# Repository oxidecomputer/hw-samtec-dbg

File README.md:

# hw-samtec-dbg

Allows for conversion between SFM-105-02-X-DH-XX, TFC-105-02-F-D-A-K, and a 2x5 0.1" header.

# Status
CAD represents a functional design without modifications

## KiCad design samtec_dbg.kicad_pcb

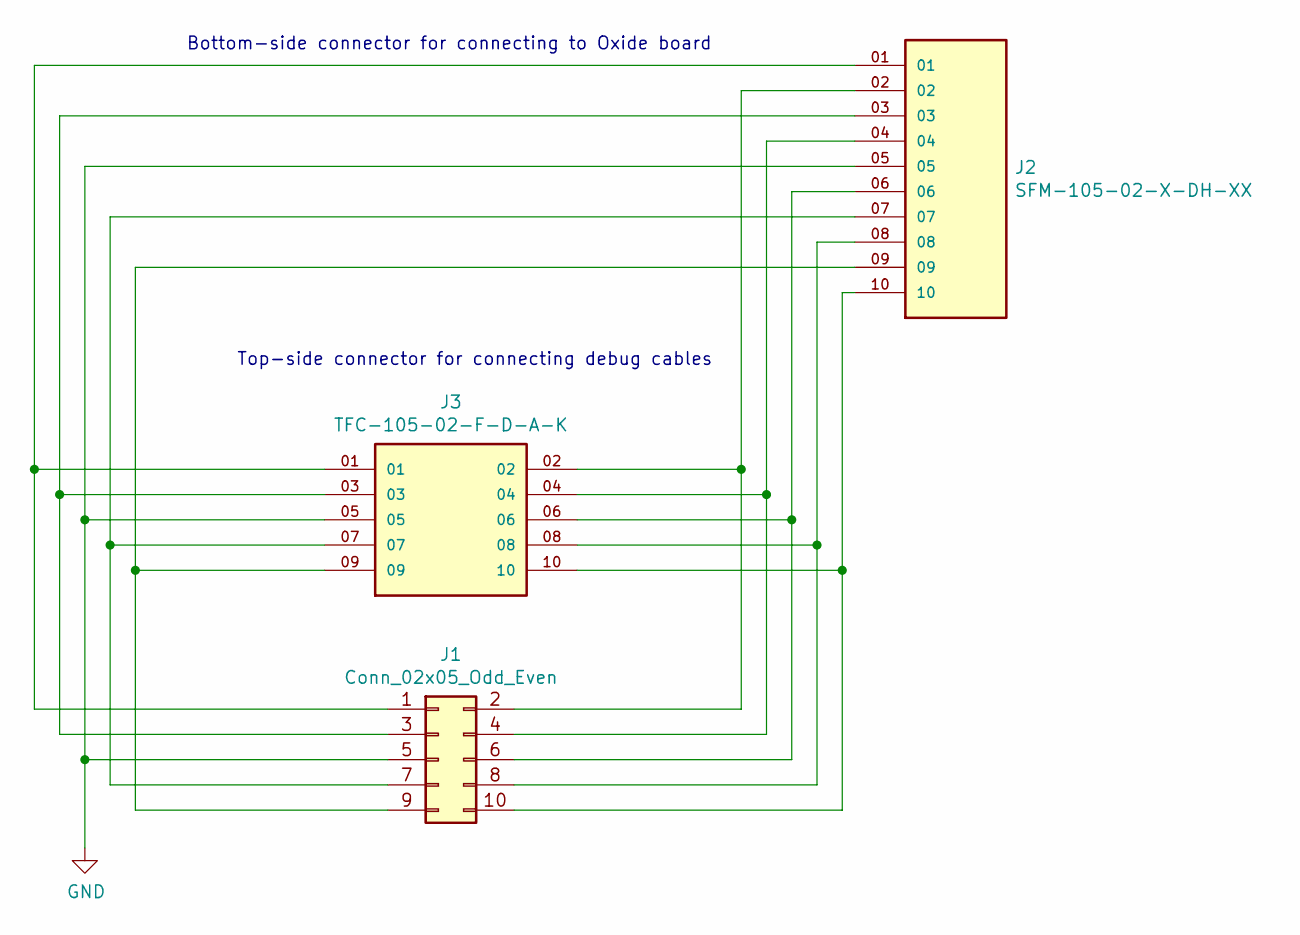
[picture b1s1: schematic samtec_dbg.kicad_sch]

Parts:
J1: Conn_02x05_Odd_Even; PinHeader_2x05_P2.54mm_Vertical_SMD
J2: SFM-105-02-X-DH-XX; SAMTEC_SFM-105-02-X-DH-XX; PARTREV D
J3: TFC-105-02-F-D-A-K; SAMTEC_TFC-105-02-F-D-A-K; PARTREV R

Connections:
GND: J1.5, J2.05, J3.05
unnamed: J1.1, J2.01, J3.01
unnamed: J1.2, J2.02, J3.02
unnamed: J1.3, J2.03, J3.03
unnamed: J1.4, J2.04, J3.04
unnamed: J1.6, J2.06, J3.06
unnamed: J1.7, J2.07, J3.07
unnamed: J1.8, J2.08, J3.08
unnamed: J1.9, J2.09, J3.09
unnamed: J1.10, J2.10, J3.10

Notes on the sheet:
Bottom-side connector for connecting to Oxide board
Top-side connector for connecting debug cables

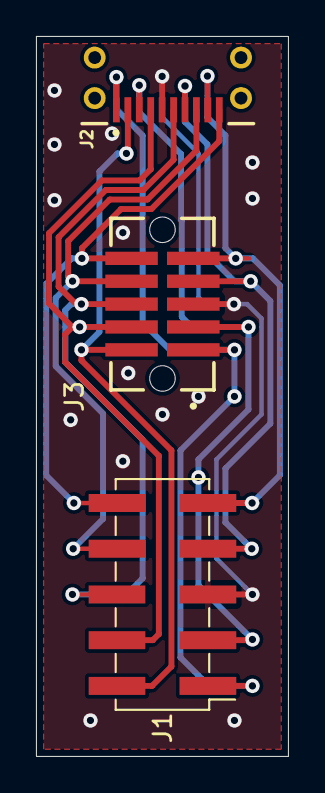
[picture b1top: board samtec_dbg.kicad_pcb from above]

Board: 4 copper layers, 14.0 x 40.0 mm, 4 parts (1 on the bottom side), 10 nets.

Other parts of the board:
Ref**: Val**; OXIDE_Wordmark

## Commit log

2023-02-24 Initial move into repo
2023-02-24 Update gitignore
